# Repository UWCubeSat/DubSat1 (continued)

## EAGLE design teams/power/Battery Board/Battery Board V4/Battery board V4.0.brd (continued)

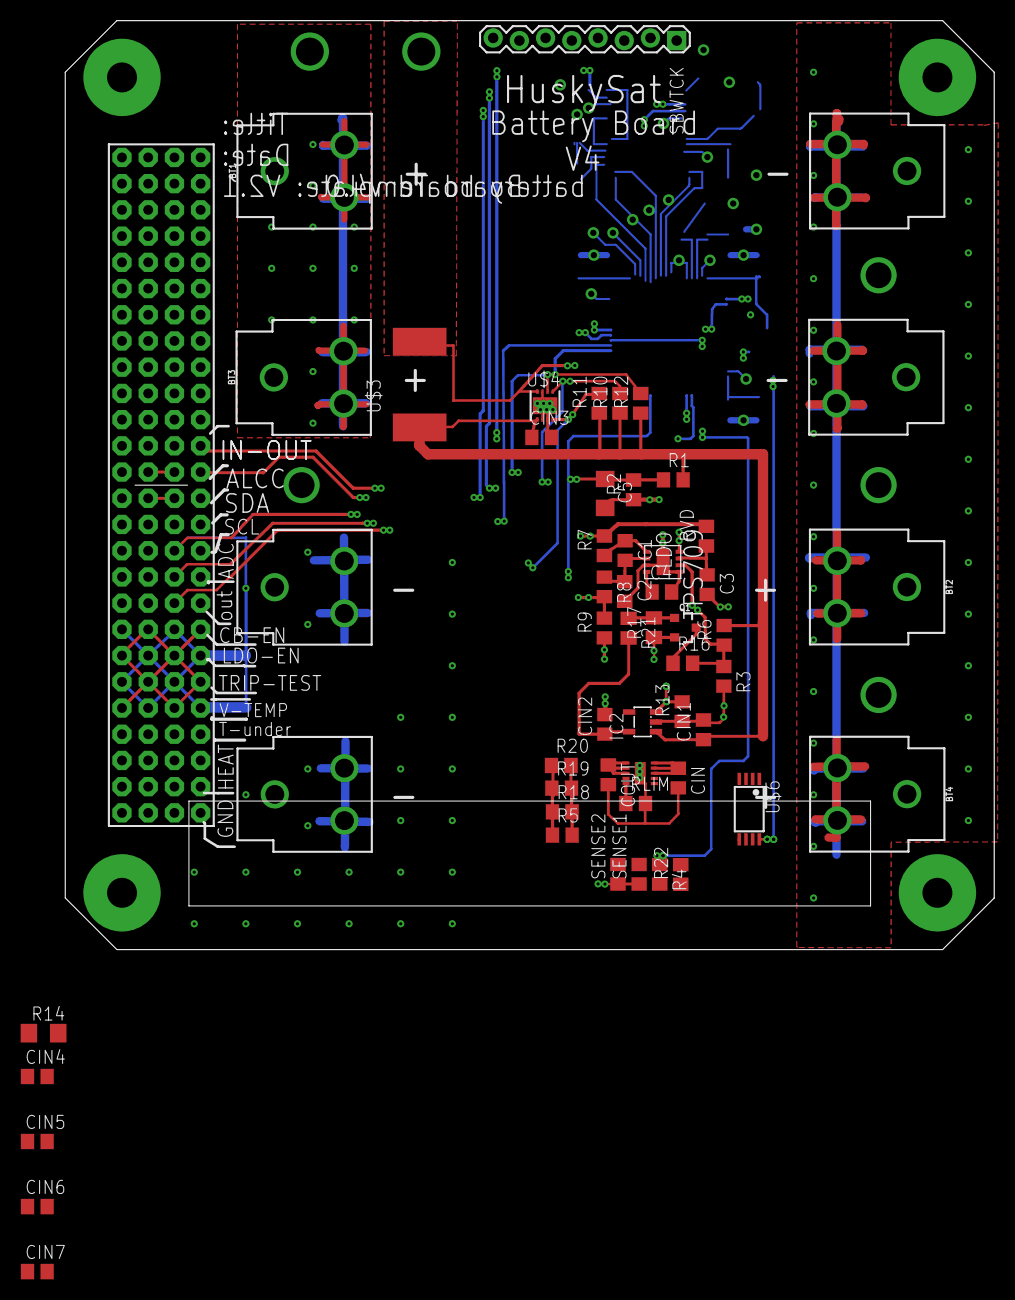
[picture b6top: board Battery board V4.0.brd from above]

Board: 4 copper layers, 90.0 x 90.0 mm, 54 parts (1 on the bottom side), 39 nets.
